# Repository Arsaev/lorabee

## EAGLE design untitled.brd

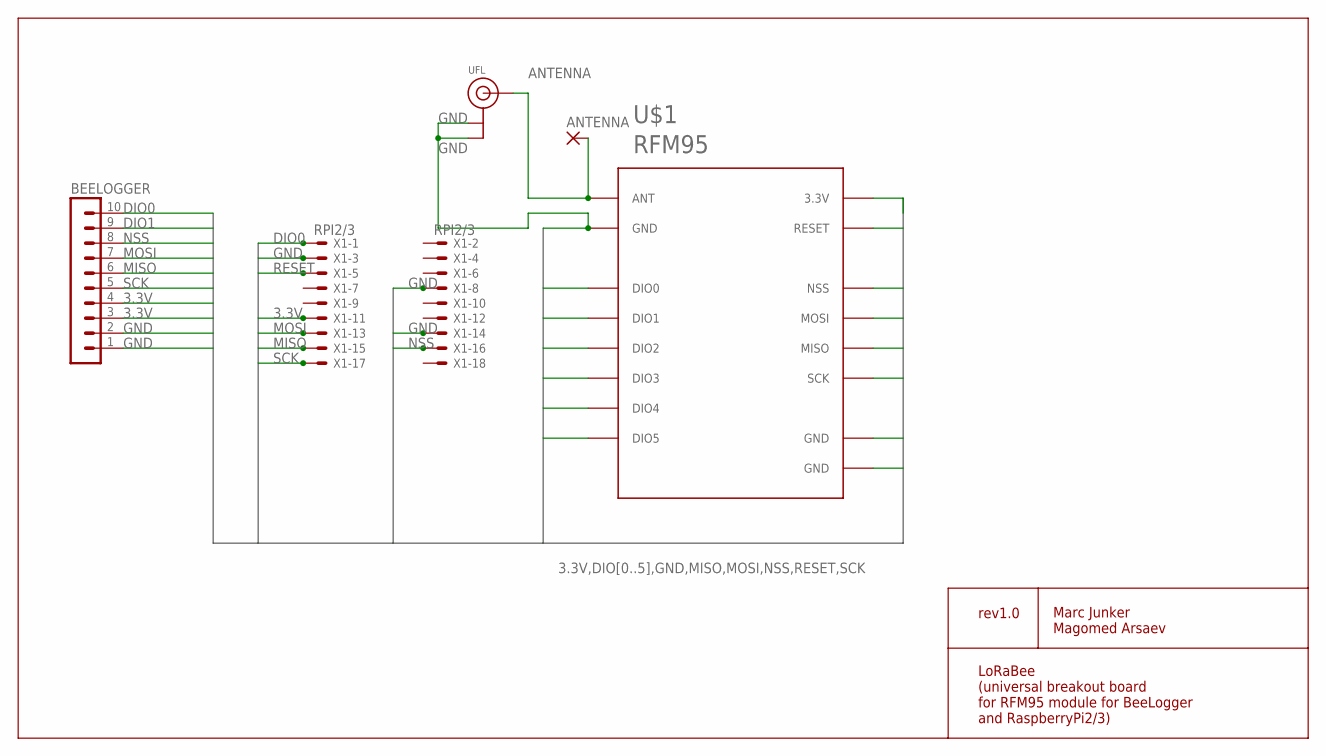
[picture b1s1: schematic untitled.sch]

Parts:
ANTENNA: 1,6/0,8
BEELOGGER: MA10-1
U$1: RFM95
UFL: ANTENNA_U.FL; U.FL
X1: RPI2/3; 332-18

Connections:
3.3V: BEELOGGER.3, BEELOGGER.4, U$1.P$13 (3.3V), X1.11
ANTENNA: ANTENNA.1, U$1.P$9 (ANT), UFL.3 (SIGNAL)
DIO0: BEELOGGER.10, U$1.P$14 (DIO0), X1.1
DIO1: BEELOGGER.9, U$1.P$15 (DIO1)
DIO2: U$1.P$16 (DIO2)
DIO3: U$1.P$11 (DIO3)
DIO4: U$1.P$12 (DIO4)
DIO5: U$1.P$7 (DIO5)
GND: BEELOGGER.1, BEELOGGER.2, U$1.P$1 (GND), U$1.P$8 (GND), U$1.P$10 (GND), UFL.1 (GND), UFL.2 (GND), X1.3, X1.8, X1.14
MISO: BEELOGGER.6, U$1.P$2 (MISO), X1.15
MOSI: BEELOGGER.7, U$1.P$3 (MOSI), X1.13
NSS: BEELOGGER.8, U$1.P$5 (NSS), X1.16
RESET: U$1.P$6 (RESET), X1.5
SCK: BEELOGGER.5, U$1.P$4 (SCK), X1.17

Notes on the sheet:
Marc Junker Magomed Arsaev
rev1.0
LoRaBee (universal breakout board for RFM95 module for BeeLogger and RaspberryPi2/3)

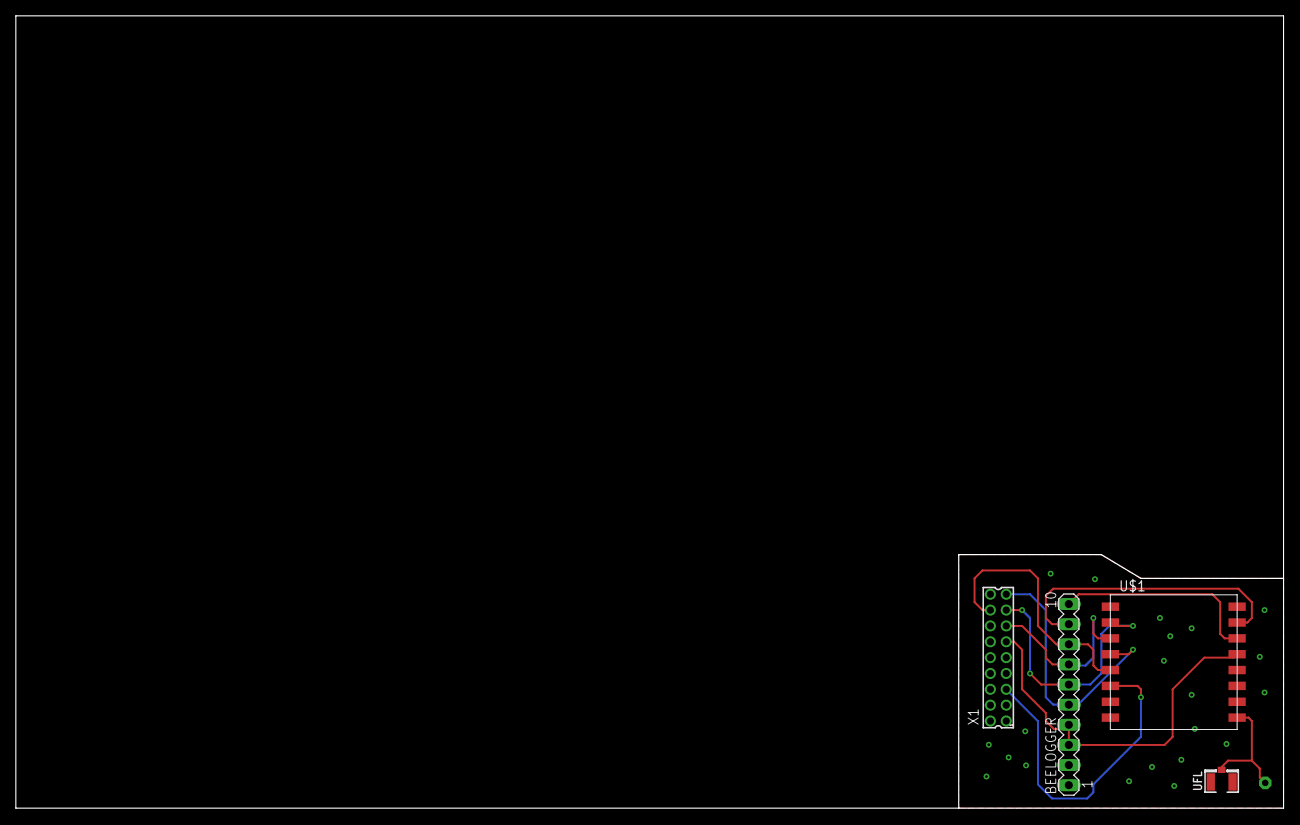
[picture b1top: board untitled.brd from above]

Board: 2 copper layers, 160.0 x 100.0 mm, 5 parts (1 on the bottom side), 10 nets.
